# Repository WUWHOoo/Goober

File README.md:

# Goober the RoboGoose

Goober is a goose I’m building because I want a little robot that’ll wander around and quack. My school is filled with groups of geese, so how can I assimilate into their society? You become them.

There are three RDS3245 servos in each leg. The hip also has a 5010 brushless motor and a cycloidal 30:1 gearbox that I designed. When I weighed the parts, the thigh came out to 20 g and the tibia was 18 g. One servo weighs 60 g, more than both prints together. Those are the numbers I’m using in the sim now that I'll talk about in the next point. The head and neck are just my best estimates. The total weight of this little thing is around 2KG.

## ☆ THE SIMULATION ☆

We live in a total simulation.

Unzip the [Goober model](simulation/Goober-MuJoCo-legs.zip). Open a terminal in the folder where you can see both `goober.xml` and `meshes`. Run these two lines there.

```sh
python -m pip install mujoco==3.3.7
python -m mujoco.viewer --mjcf=goober.xml
```

That opens the viewer so you can move the camera around and look at the eight leg joints.

To train the model, I relied on Google's CoLab. [Walking notebook](https://colab.research.google.com/github/WUWHOoo/Goober/blob/main/simulation/Train-Goober-Gait.ipynb) · [Starting policy ZIP](simulation/Goober-PPO-printed.zip) · [Robot ZIP](simulation/Goober-MuJoCo-legs.zip)

### Watch Goober in MuJoCo

- [Recording 1 · 12:41:11](simulation/Screen%20Recording%202026-11-20%20124111.mp4)
- [Recording 2 · 12:46:42](simulation/Screen%20Recording%202026-11-20%20124642.mp4)
- [Recording 3 · 14:14:22](simulation/Screen%20Recording%202026-11-20%20141422.mp4)

## What’s inside

The Fusion file has the whole goose. If you just want to see how the hip works, the gearbox has its own STEP file. The actuator ZIP has the printable pieces, down to the little shim for the encoder. [Fusion assembly](CAD/Goober.f3d) · [Gearbox STEP](CAD/Cyloidal%20Drive.step) · [Actuator STLs](CAD/Goober-Actuator-v3-STLs.zip)

I made a two-layer 2.5 oz copper PCB for the STM32H723, radio, servos and both motor drivers. Each side gets its own 8.4 V buck converter for the leg servos and a third converter supplies 5 V. 

[KiCad 10 project](PCB/PDB.kicad_pro) · [Gerbers and drill file](PCB/gerbers.zip) · [Parts list](bom.csv)

## First power-up

The only firmware here so far is a little USB test. Send the board a `?` and it should tell you how long it’s been on. I haven’t tried it on Goober yet. [Arduino sketch](firmware/GooberBringup/GooberBringup.ino)

To try it, leave motor power disconnected. In the Arduino IDE, pick your STM32H723 board from the STM32duino core, enable USB CDC as the generic Serial port and upload the sketch. Open Serial Monitor at 115200 baud to send the `?`.

I’ll add photos and a demo once I have the real goose walking.

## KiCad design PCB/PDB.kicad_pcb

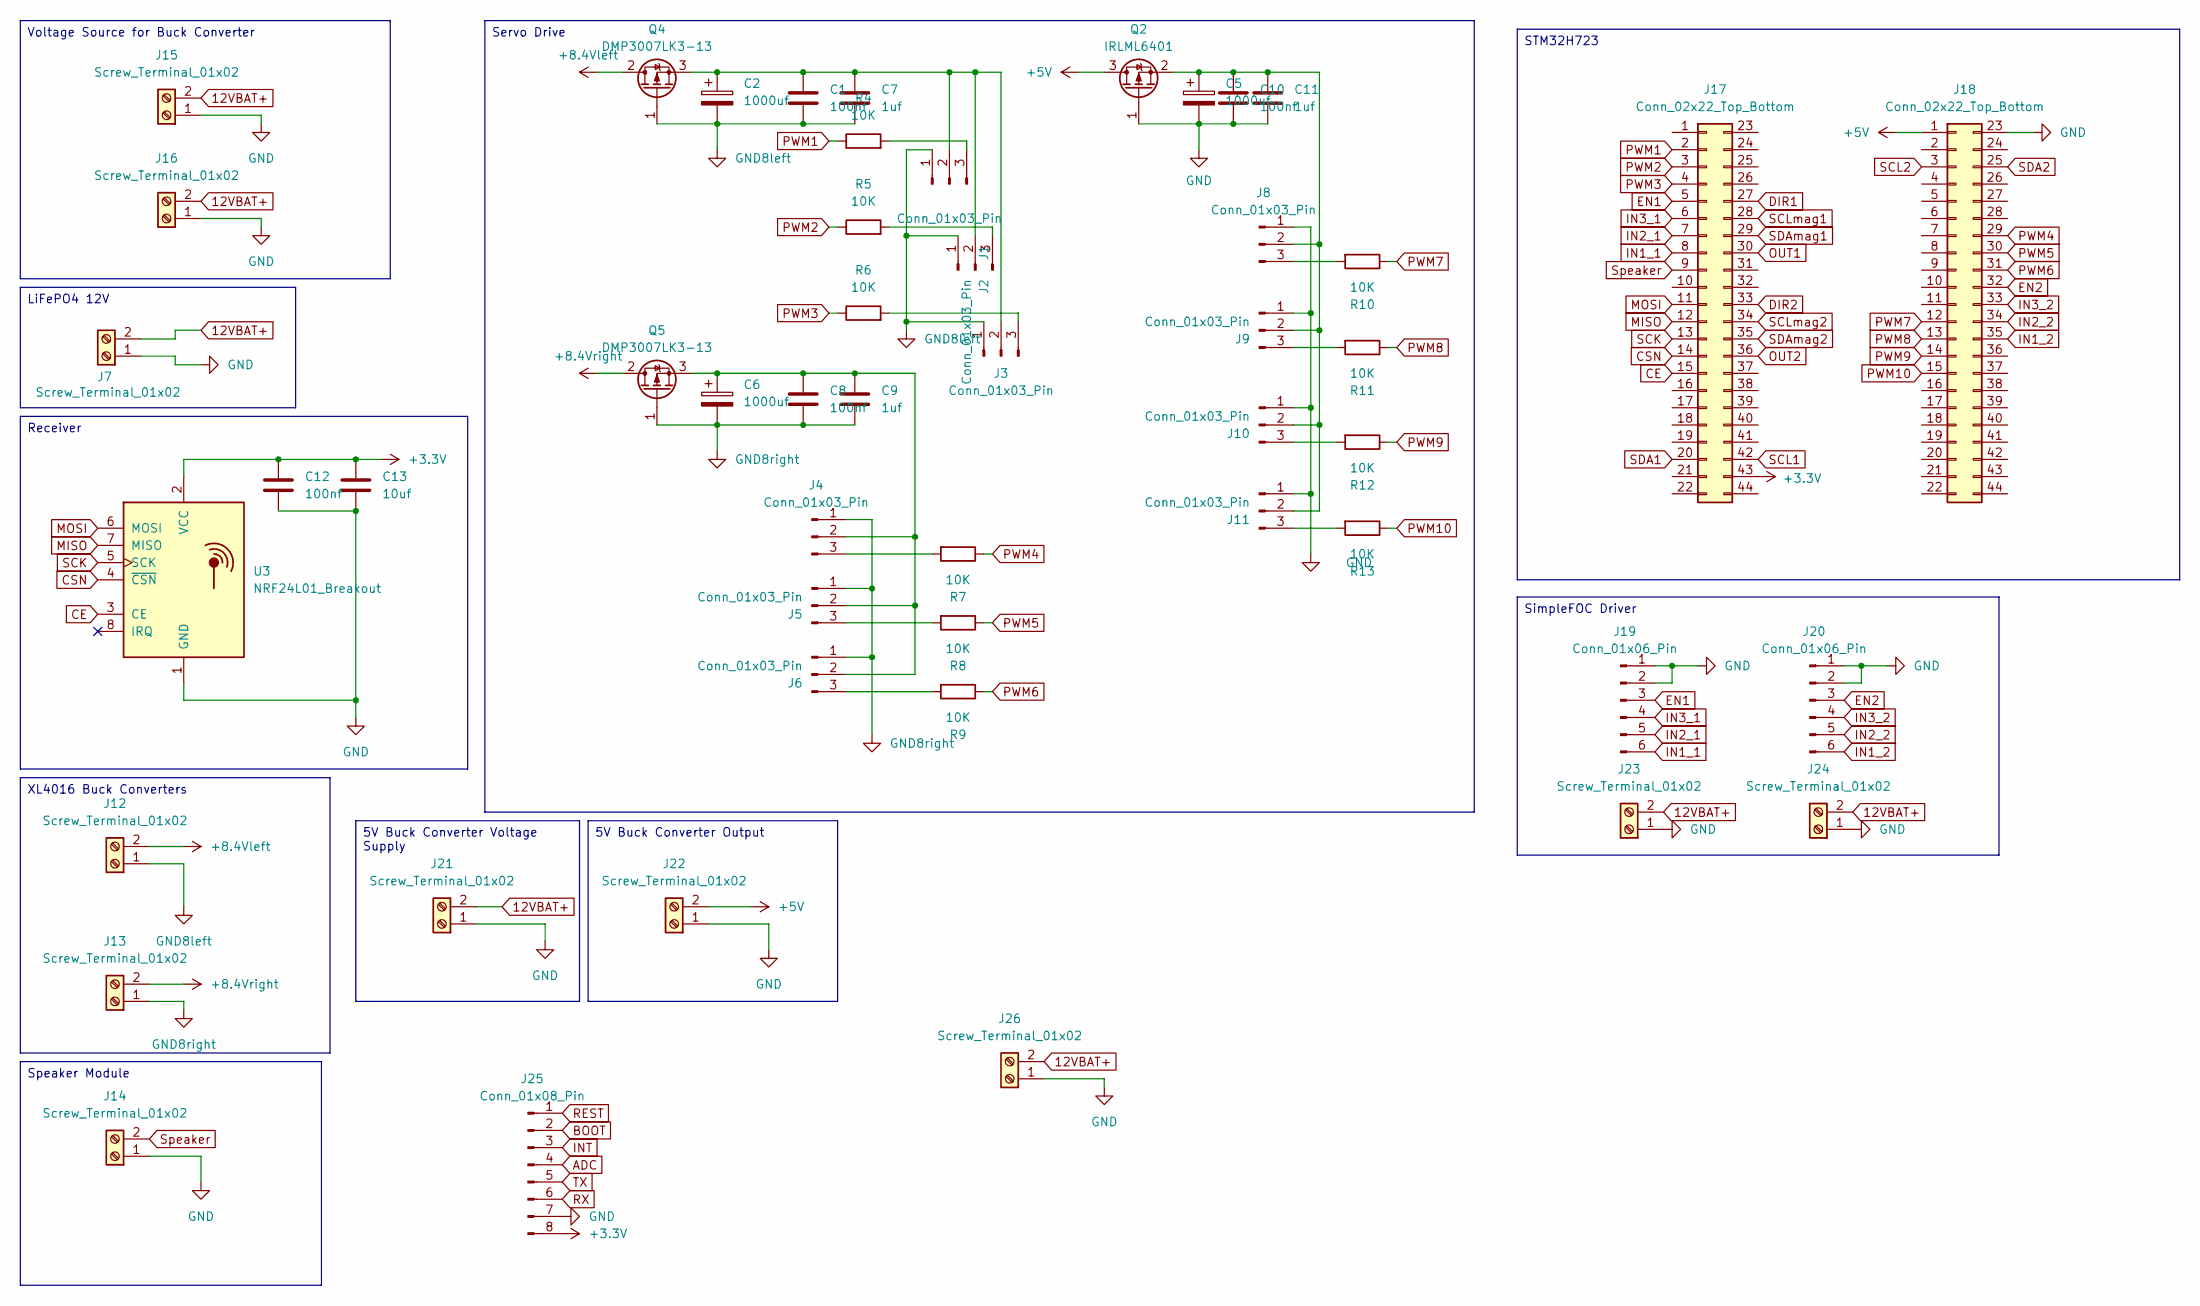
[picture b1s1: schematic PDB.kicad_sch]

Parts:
C1, C8, C10, C12: 100nf; C_Radial_D5.0mm_H11.0mm_P2.00mm
C2, C5, C6: 1000uf; CP_Radial_D13.0mm_P5.00mm
C7, C9, C11: 1uf; C_Radial_D5.0mm_H11.0mm_P2.00mm
C13: 10uf; C_Radial_D5.0mm_H11.0mm_P2.00mm
J1, J2, J3, J4, J5, J6, J8, J9, J10, J11: Conn_01x03_Pin; PinHeader_1x03_P2.54mm_Vertical
J7, J12, J13, J14, J15, J16, J21, J22, J23, J24, J26: Screw_Terminal_01x02; TerminalBlock_MetzConnect_Type011_RT05502HBLC_1x02_P5.00mm_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
J17, J18: Conn_02x22_Top_Bottom; PinHeader_2x22_P2.54mm_Vertical
J19, J20: Conn_01x06_Pin; PinHeader_1x06_P2.54mm_Vertical
J25: Conn_01x08_Pin; PinSocket_1x08_P2.54mm_Vertical
Q2: IRLML6401; SOT-23
Q4, Q5: DMP3007LK3-13; TO-252-2
R4, R5, R6, R7, R8, R9, R10, R11, R12, R13: 10K; R_Box_L8.4mm_W2.5mm_P5.08mm
U3: NRF24L01_Breakout; nRF24L01_Breakout

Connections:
12VBAT+: J7.2, J15.2, J16.2, J21.2, J23.2, J24.2, J26.2
+3.3V: C12.1, C13.1, J17.43, J25.8, U3.2 (VCC)
+5V: J18.1, J22.2, Q2.3 (D)
+8.4Vleft: J12.2, Q4.2 (D)
+8.4Vright: J13.2, Q5.2 (D)
ADC: J25.4
BOOT: J25.2
CE: J17.15, U3.3 (CE)
CSN: J17.14, U3.4 (~CSN)
DIR1: J17.27
DIR2: J17.33
EN1: J17.5, J19.3
EN2: J18.32, J20.3
GND: C5.2, C10.2, C11.2, C12.2, C13.2, J7.1, J8.1, J9.1, J10.1, J11.1, J14.1, J15.1, J16.1, J18.23, J19.1, J19.2, J20.1, J20.2, J21.1, J22.1, J23.1, J24.1, J25.7, J26.1, Q2.1 (G), U3.1 (GND)
GND8left: C1.2, C2.2, C7.2, J1.1, J2.1, J3.1, J12.1, Q4.1 (G)
GND8right: C6.2, C8.2, C9.2, J4.1, J5.1, J6.1, J13.1, Q5.1 (G)
IN1_1: J17.8, J19.6
IN1_2: J18.35, J20.6
IN2_1: J17.7, J19.5
IN2_2: J18.34, J20.5
IN3_1: J17.6, J19.4
IN3_2: J18.33, J20.4
INT: J25.3
MISO: J17.12, U3.7 (MISO)
MOSI: J17.11, U3.6 (MOSI)
unnamed: C1.1, C2.1, C7.1, J1.2, J2.2, J3.2, Q4.3 (S)
unnamed: J1.3, R4.2
unnamed: J2.3, R5.2
unnamed: J3.3, R6.2
unnamed: C6.1, C8.1, C9.1, J4.2, J5.2, J6.2, Q5.3 (S)
unnamed: J4.3, R7.2
unnamed: J5.3, R8.2
unnamed: J6.3, R9.2
unnamed: J8.3, R10.2
unnamed: J9.3, R11.2
unnamed: C5.1, C10.1, C11.1, J8.2, J9.2, J10.2, J11.2, Q2.2 (S)
unnamed: J10.3, R12.2
unnamed: J11.3, R13.2
OUT1: J17.30
OUT2: J17.36
PWM1: J17.2, R4.1
PWM2: J17.3, R5.1
PWM3: J17.4, R6.1
PWM4: J18.29, R7.1
PWM5: J18.30, R8.1
PWM6: J18.31, R9.1
PWM7: J18.12, R10.1
PWM8: J18.13, R11.1
PWM9: J18.14, R12.1
PWM10: J18.15, R13.1
REST: J25.1
RX: J25.6
SCK: J17.13, U3.5 (SCK)
SCL1: J17.42
SCL2: J18.3
SCLmag1: J17.28
SCLmag2: J17.34
SDA1: J17.20
SDA2: J18.25
SDAmag1: J17.29
SDAmag2: J17.35
Speaker: J14.2, J17.9
TX: J25.5

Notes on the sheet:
Voltage Source for Buck Converter
SimpleFOC Driver
Servo Drive
Receiver
5V Buck Converter Voltage Supply
XL4016 Buck Converters
Speaker Module
5V Buck Converter Output
STM32H723
LiFePO4 12V

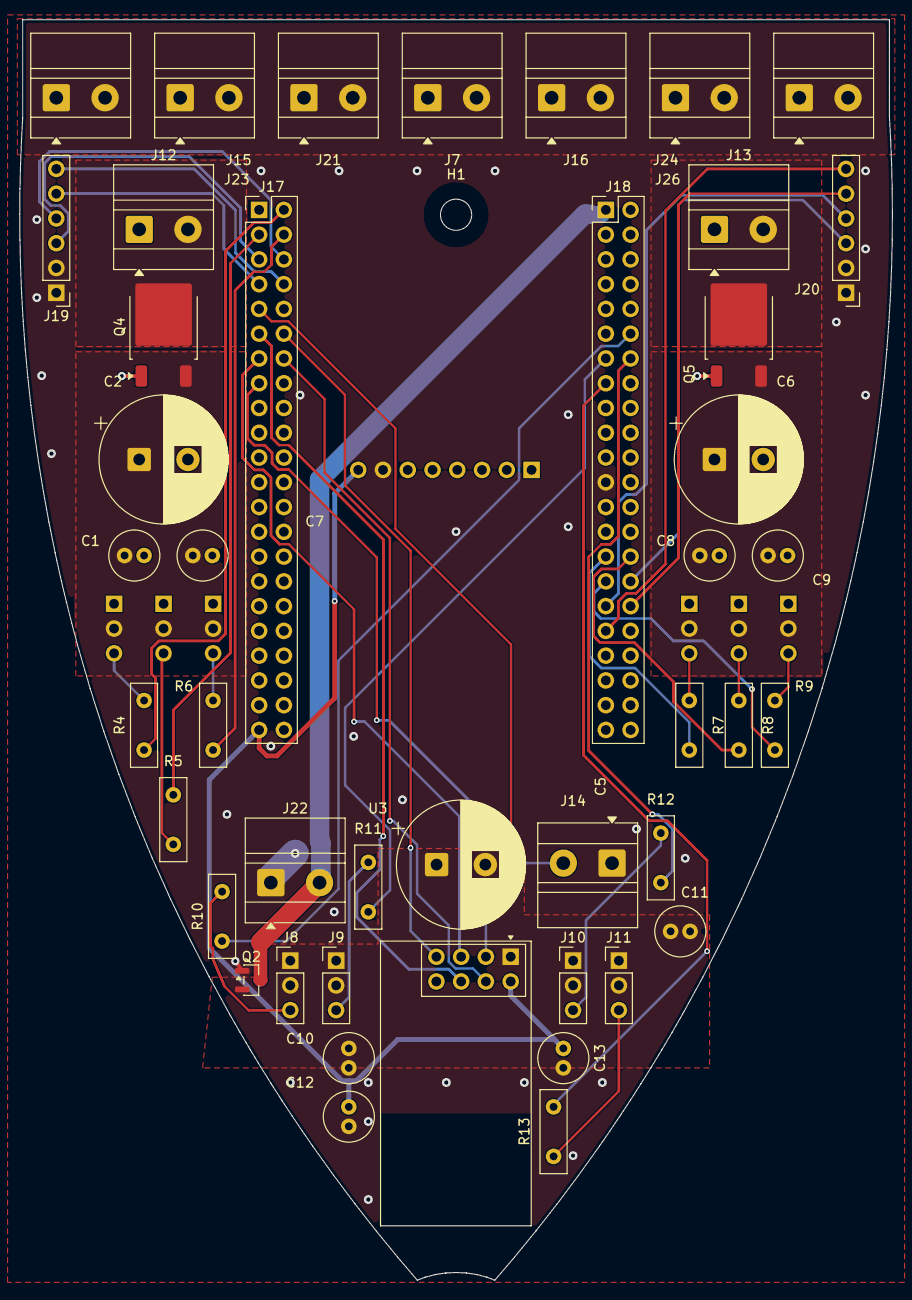
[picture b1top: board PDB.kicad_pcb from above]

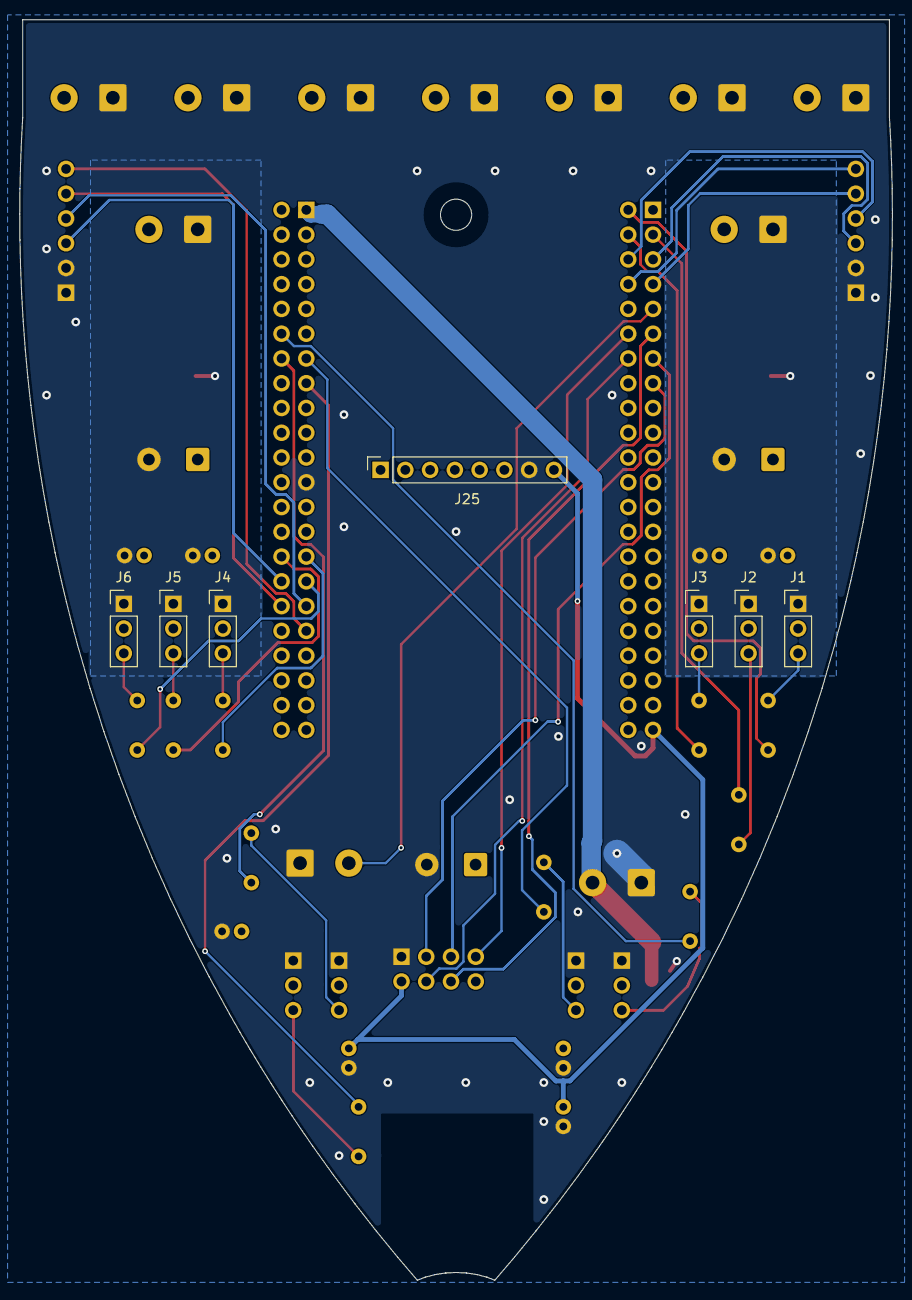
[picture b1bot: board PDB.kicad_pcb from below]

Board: 2 copper layers, 89.5 x 129.3 mm, 52 parts (7 on the bottom side), 45 nets.

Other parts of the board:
H1: MountingHole_3.2mm_M3

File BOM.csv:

"Group","Item","Quantity","References or use","Design or sourcing link","Ownership","Selection notes"
"PCB","100 nF radial capacitor","4","C1 C8 C10 C12","https://www.digikey.com/en/products/result?keywords=100%20nF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","Unconfirmed","Capacitor_THT:C_Radial_D5.0mm_H11.0mm_P2.00mm"
"PCB","1000 uF polarized radial capacitor","3","C2 C5 C6","https://www.digikey.com/en/products/result?keywords=1000%20u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","Unconfirmed","Capacitor_THT:CP_Radial_D13.0mm_P5.00mm"
"PCB","1 uF radial capacitor","3","C7 C9 C11","https://www.digikey.com/en/products/result?keywords=1%20uF%2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","Unconfirmed","Capacitor_THT:C_Radial_D5.0mm_H11.0mm_P2.00mm"
"PCB","10 uF radial capacitor","1","C13","https://www.digikey.com/en/products/result?keywords=10%20uF%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","Unconfirmed","Capacitor_THT:C_Radial_D5.0mm_H11.0mm_P2.00mm"
"PCB","1x3 male header 2.54 mm","10","J1 J2 J3 J4 J5 J6 J8 J9 J10 J11","https://www.digikey.com/en/products/result?keywords=1x3%20ma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","Unconfirmed","Connector_PinHeader_2.54mm:PinHeader_1x03_P2.54mm_Vertical"
"PCB","2-position terminal block 5 mm","11","J7 J12 J13 J14 J15 J16 J21 J22 J23 J24 J26","https://www.digikey.com/en/products/result?keywords=2-positi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","Unconfirmed","TerminalBlock_MetzConnect:TerminalBlock_MetzConnect_Type011_RT05502HBLC_1x02_P5.00mm_Horizontal (placeholder; final terminal TBD)"
"PCB","2x22 header 2.54 mm","2","J17 J18","https://www.digikey.com/en/products/result?keywords=2x22%20h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","Unconfirmed","Connector_PinHeader_2.54mm:PinHeader_2x22_P2.54mm_Vertical"
"PCB","1x6 male header 2.54 mm","2","J19 J20","https://www.digikey.com/en/products/result?keywords=1x6%20ma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","Unconfirmed","Connector_PinHeader_2.54mm:PinHeader_1x06_P2.54mm_Vertical"
"PCB","1x8 female socket 2.54 mm","1","J25","https://www.digikey.com/en/products/result?keywords=1x8%20fe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","Unconfirmed","Connector_PinSocket_2.54mm:PinSocket_1x08_P2.54mm_Vertical"
"PCB","IRLML6401","1","Q2","https://www.digikey.com/en/products/result?keywords=IRLML6401","Unconfirmed","Package_TO_SOT_SMD:SOT-23"
"PCB","DMP3007LK3-13","2","Q4 Q5","https://www.digikey.com/en/products/result?keywords=DMP3007LK3-13","Unconfirmed","Package_TO_SOT_SMD:TO-252-2"
"PCB","10 kOhm through-hole resistor","10","R4 R5 R6 R7 R8 R9 R10 R11 R12 R13","https://www.digikey.com/en/products/result?keywords=10%20kOh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","Unconfirmed","Resistor_THT:R_Box_L8.4mm_W2.5mm_P5.08mm"
"PCB","nRF24L01 breakout","1","U3","https://www.digikey.com/en/products/result?keywords=nRF24L01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","Unconfirmed","RF_Module:nRF24L01_Breakout"
"Robot","Goober carrier PCB","1","Power distribution","https://github.com/WUWHOoo/Goober/tree/main/PCB","Unconfirmed","Two-layer custom board"
"Robot","STM32H723 development board","1","Controller","https://www.aliexpress.com/wholesale?SearchText=STM32H723VGT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","Unconfirmed","Verify header numbering and board revision"
"Robot","RDS3245 servo","6","Three per leg","https://www.aliexpress.com/wholesale?SearchText=RDS3245%20servo","Unconfirmed","60 g measured per motor"
"Robot","5010 brushless motor","2","One per hip gearbox","https://www.aliexpress.com/wholesale?SearchText=5010%20brush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","Unconfirmed","93 g per motor; winding variant unconfirmed"
"Robot","SimpleFOCMini v2.3","2","5010 motor drivers","https://docs.simplefoc.com/simplefocmini","Unconfirmed",""
"Robot","AS5600 encoder module","2","Hip encoders","https://www.aliexpress.com/wholesale?SearchText=AS5600%20mag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","Unconfirmed","Check magnet and mounting"
"Robot","XL4016 adjustable buck module","2","Left and right 8.4 V banks","https://www.aliexpress.com/wholesale?SearchText=XL4016%20CC%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","Unconfirmed","Size against measured load"
"Robot","Mini560 Pro 5 V","1","5 V rail","https://www.aliexpress.com/wholesale?SearchText=Mini560%20Pr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","Unconfirmed","Fixed 5 V version"
"Robot","12 V nominal LiFePO4 battery","1","J7","https://www.aliexpress.com/wholesale?SearchText=12V%20LiFePO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","Unconfirmed","Capacity and specific pack unconfirmed"
"Robot","Cooling fan","1","Torso fan","https://www.aliexpress.com/wholesale?SearchText=DC%20brushle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","Unconfirmed","Verify voltage, dimensions and hole spacing"
"Robot","Speaker module","1","Quack output","https://www.aliexpress.com/wholesale?SearchText=speaker%20mo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","Unconfirmed","Model unconfirmed"
"Robot","FS90R micro servo","2","CAD reference","https://www.aliexpress.com/wholesale?SearchText=FEETECH%20FS90R","Unconfirmed","Model and quantity from CAD; confirm installed selection"
"Robot","GS Power 21 g servo","2","CAD reference","https://www.aliexpress.com/wholesale?SearchText=GS%20Power%2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","Unconfirmed","Confirm installed selection"
"Robot","Printed body, lid, head, bill, neck, thighs, tibias and feet","Set","Custom printed structure","https://github.com/WUWHOoo/Goober/tree/main/CAD","Unconfirmed","Some parts printed and weighed; final material and inventory unconfirmed"
"Robot","Printed cycloidal actuator parts","2","One set per leg","https://github.com/WUWHOoo/Goober/blob/main/CAD/Goober-Actua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","Unconfirmed","Ten distinct print files per set; follow shim filename"
"Robot","Assembly fasteners, bearings, magnets and wiring","TBD","Actuators and body","https://github.com/WUWHOoo/Goober/blob/main/CAD/Goober.f3d","Unconfirmed","Reference geometry; individual quantities and order codes pending"
